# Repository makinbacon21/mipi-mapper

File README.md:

# MIPI Mapper

Adapts between BM23PF0.8-40DP-0.35V microdisplay interface and 31-pin ribbon DSI. WIP.

## Info

For ENGR 090 undergraduate engineering capstone project

Thomas Makin, Xezel Peshlakai, Swarthmore College Class of 2025

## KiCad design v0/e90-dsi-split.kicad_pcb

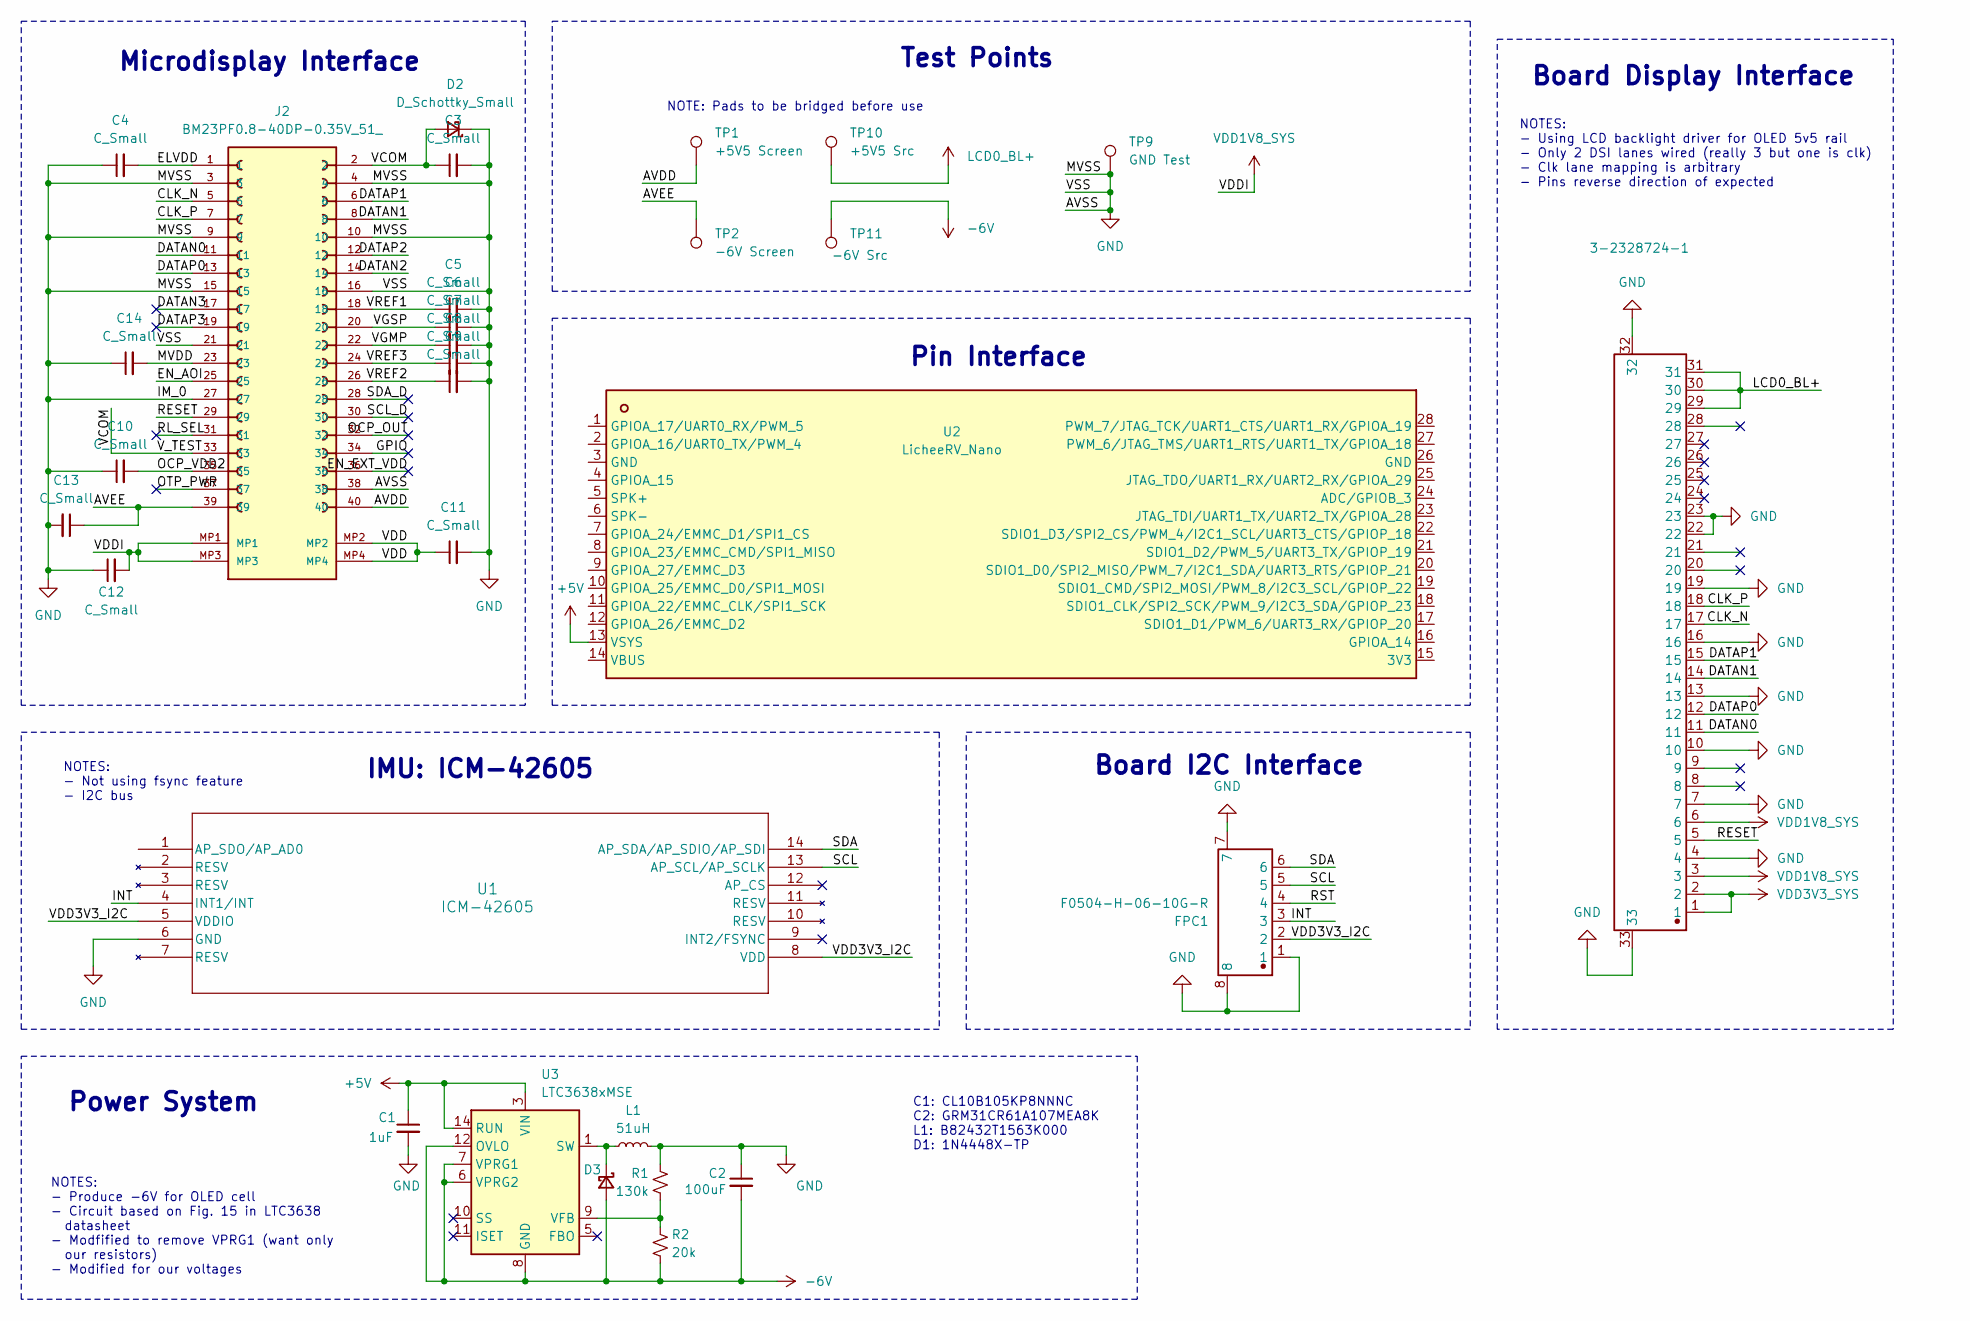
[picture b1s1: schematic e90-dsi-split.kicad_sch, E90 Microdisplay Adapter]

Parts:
C1: 1uF; C_0603_1608Metric
C2: 100uF; C_1206_3216Metric
C3, C4, C5, C6, C7, C8, C9, C10, C11, C12, C13, C14: C_Small; C_0603_1608Metric
D2, D3: D_Schottky_Small; D_SOD-123
FPC1: F0504-H-06-10G-R; FFC-SMD_6P-P0.50_F0504-H-06-10G-R; Manufacturer Part F0504-H-06-10G-R
J1: 3-2328724-1; FPC-SMD_31P-P0.30_HDGC_0.3K-QX-31PWB; PARTREV 3
J2: BM23PF0.8-40DP-0.35V_51_; BM23PF0840DS035V51-GOOD
L1: 51uH; L_1812_4532Metric
R1: 130k; R_0603_1608Metric
R2: 20k; R_0603_1608Metric
TP1: +5V5 Screen; TestPoint_Pad_1.0x1.0mm
TP2: -6V Screen; TestPoint_Pad_1.0x1.0mm
TP9: GND Test; TestPoint_Pad_1.0x1.0mm
TP10: +5V5 Src; TestPoint_Pad_1.0x1.0mm
TP11: -6V Src; TestPoint_Pad_1.0x1.0mm
U1: ICM-42605; LGA14_2P5X3X0P91_IVS
U2: LicheeRV_Nano
U3: LTC3638xMSE; Analog_MSOP-12-16-1EP_3x4.039mm_P0.5mm_EP1.651x2.845mm

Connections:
+5V: C1.1, U2.13 (VSYS), U3.3 (VIN), U3.14 (RUN)
-6V: C2.2, D3.2 (A), R2.2, TP11.1, U3.6 (VPRG2), U3.7 (VPRG1), U3.8 (GND), U3.12 (OVLO), U3.16 (GND), U3.17 (GND)
/AVDD: J2.40, TP1.1
/AVEE: C13.1, J2.39, TP2.1
/CLK_N: J1.17, J2.5
/CLK_P: J1.18, J2.7
/DATAN0: J1.11, J2.11
/DATAN1: J1.14, J2.8
/DATAN2: J2.14
/DATAN3: J2.17
/DATAP0: J1.12, J2.13
/DATAP1: J1.15, J2.6
/DATAP2: J2.12
/DATAP3: J2.19
/ELVDD: C4.2, J2.1
/EN_AOI: J2.25
/EN_EXT_VDD: J2.36
/GPIO: J2.34
/INT: FPC1.3, U1.4 (INT1/INT)
/MVDD: C14.2, J2.23
/OCP_OUT: J2.32
/OCP_VDD2: C10.2, J2.35
/OTP_PWR: J2.37
/RESET: J1.5, J2.29
/RL_SEL: J2.31
/RST: FPC1.4
/SCL: FPC1.5, U1.13 (AP_SCL/AP_SCLK)
/SCL_D: J2.30
/SDA: FPC1.6, U1.14 (AP_SDA/AP_SDIO/AP_SDI)
/SDA_D: J2.28
/VCOM: C3.1, D2.2 (A), J2.2, J2.33
/VDD: C11.1, J2.MP2, J2.MP4
/VDD3V3_I2C: FPC1.2, U1.5 (VDDIO), U1.8 (VDD)
/VGMP: C7.1, J2.22
/VGSP: C6.1, J2.20
/VREF1: C5.1, J2.18
/VREF2: C9.1, J2.26
/VREF3: C8.1, J2.24
GND: C1.2, C2.1, C3.2, C4.1, C5.2, C6.2, C7.2, C8.2, C9.2, C10.1, C11.2, C12.1, C13.2, C14.1, D2.1 (K), FPC1.1, FPC1.7, FPC1.8, J1.4, J1.7, J1.10, J1.13, J1.16, J1.19, J1.22, J1.23, J1.32, J1.33, J2.3, J2.4, J2.9, J2.10, J2.15, J2.16, J2.21, J2.27, J2.38, L1.2, R1.1, TP9.1, U1.6 (GND)
LCD0_BL+: J1.29, J1.30, J1.31, TP10.1
unnamed: D3.1 (K), L1.1, U3.1 (SW)
unnamed: R1.2, R2.1, U3.9 (VFB)
VDD1V8_SYS: C12.2, J1.3, J1.6, J2.MP1, J2.MP3
VDD3V3_SYS: J1.1, J1.2

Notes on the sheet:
NOTES: - Not using fsync feature - I2C bus
Board Display Interface
Power System
NOTE: Pads to be bridged before use
Test Points
NOTES: - Using LCD backlight driver for OLED 5v5 rail - Only 2 DSI lanes wired (really 3 but one is clk) - Clk lane mapping is arbitrary - Pins reverse direction of expected
Board I2C Interface
Pin Interface
NOTES: - Produce -6V for OLED cell - Circuit based on Fig. 15 in LTC3638 datasheet - Modfified to remove VPRG1 (want only our resistors) - Modified for our voltages
IMU: ICM-42605
Microdisplay Interface
C1: CL10B105KP8NNNC C2: GRM31CR61A107MEA8K L1: B82432T1563K000 D1: 1N4448X-TP

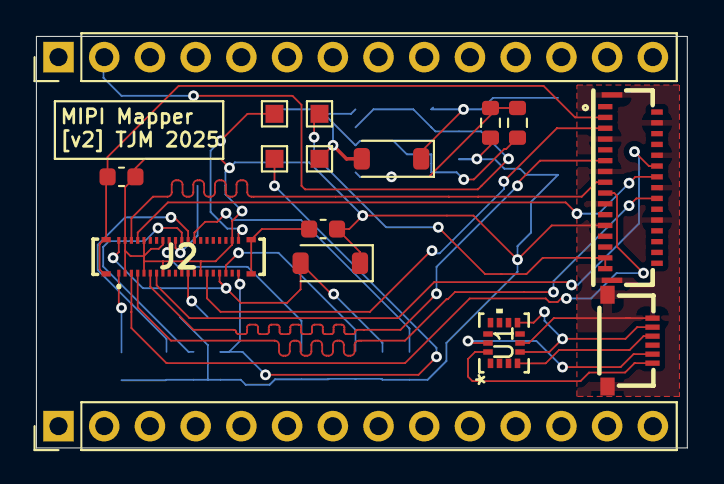
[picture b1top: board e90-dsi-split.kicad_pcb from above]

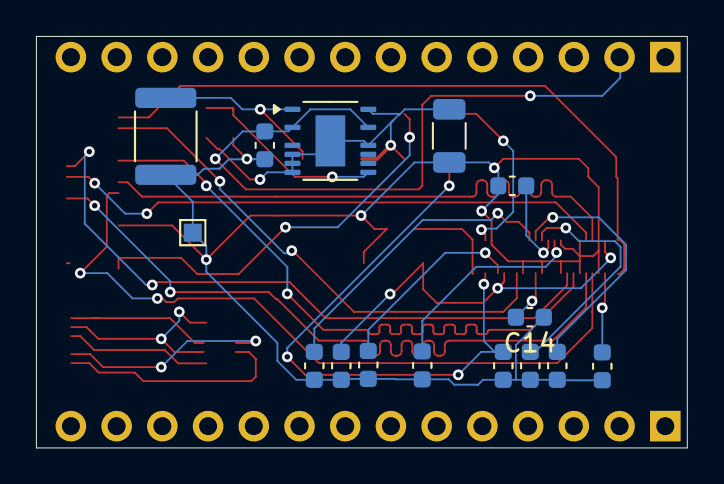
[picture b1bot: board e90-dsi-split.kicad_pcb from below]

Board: 2 copper layers, 36.2 x 22.9 mm, 29 parts (15 on the bottom side), 31 nets.

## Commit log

2024-12-14 initial commmit
2025-03-31 next
2025-04-06 misc updates, move to v1
2025-04-07 v1 updates
2025-04-09 v1: hopefully final
2025-04-25 updates post rework
2025-04-27 v2: start v2
2025-04-28 v2: continue
2025-04-30 v2: more updates
